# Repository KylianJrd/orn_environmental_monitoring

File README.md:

# orn_environmental_monitoring

ce projet va faire une station météo

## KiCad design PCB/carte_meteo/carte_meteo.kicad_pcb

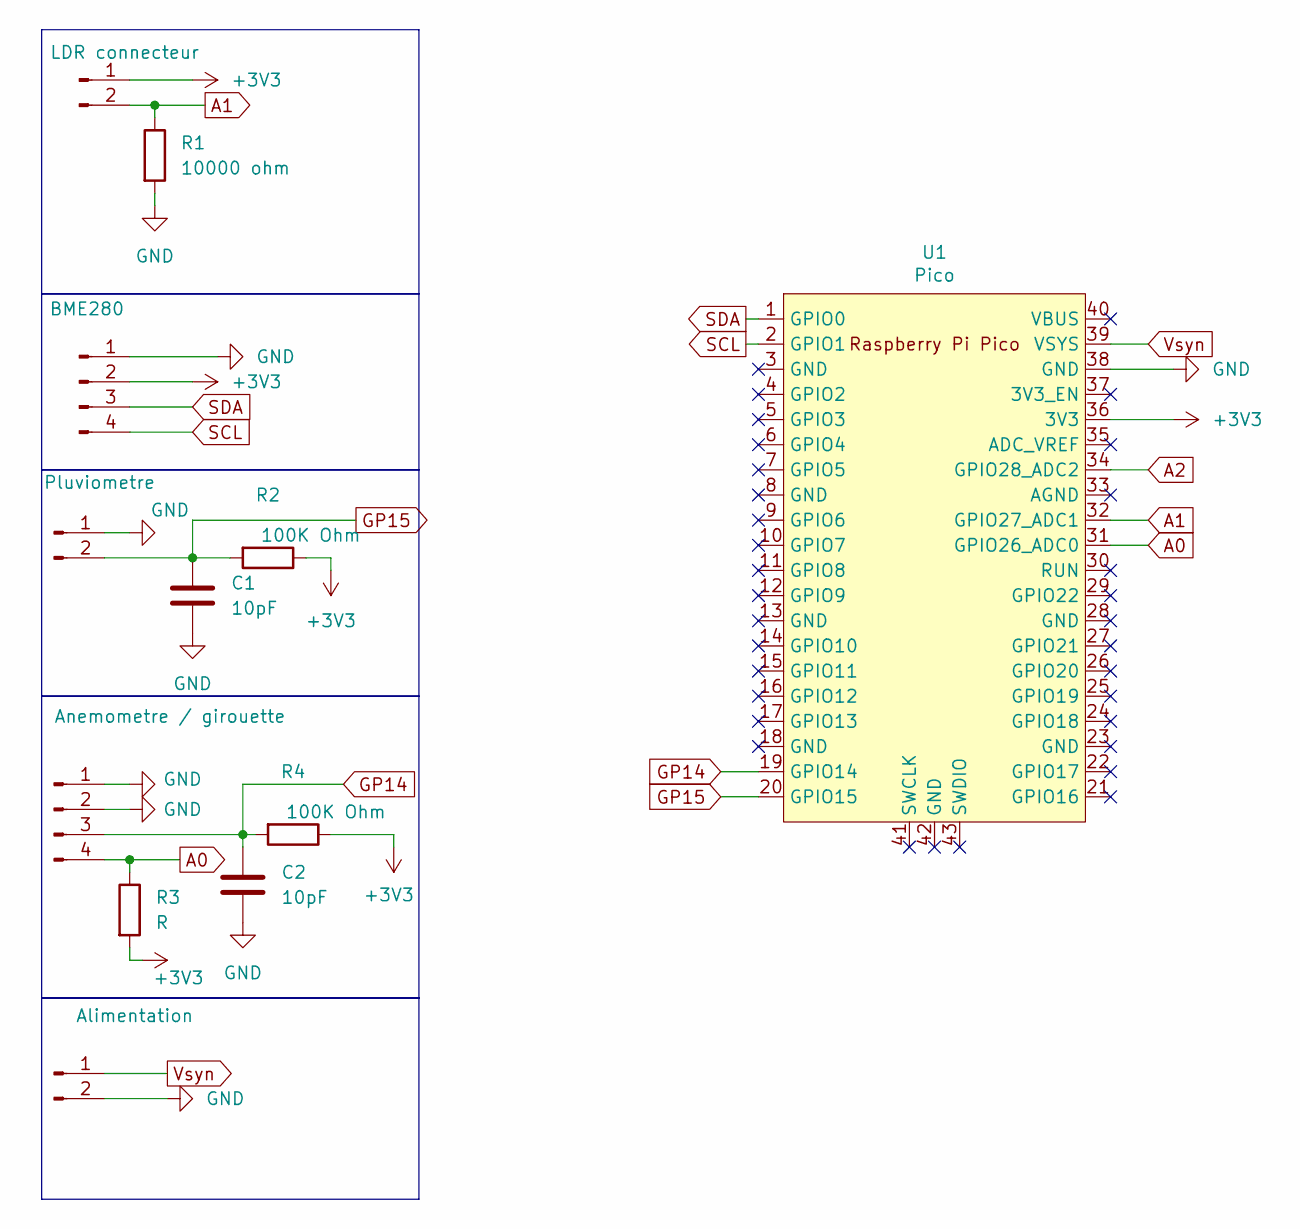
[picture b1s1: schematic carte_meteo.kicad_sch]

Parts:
C1, C2: 10pF; C_0805_2012Metric
J1: BME280; TerminalBlock_Phoenix_MKDS-1,5-4-5.08_1x04_P5.08mm_Horizont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
J2: LDR connecteur; TerminalBlock_Phoenix_MKDS-1,5-2-5.08_1x02_P5.08mm_Horizont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
J3: Pluviometre; TerminalBlock_Phoenix_MKDS-1,5-2-5.08_1x02_P5.08mm_Horizont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
J4: Anemometre / girouette; TerminalBlock_Phoenix_MKDS-1,5-4-5.08_1x04_P5.08mm_Horizont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
J5: Alimentation; TerminalBlock_Phoenix_MKDS-1,5-2-5.08_1x02_P5.08mm_Horizont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
R1: 10000 ohm; R_Axial_DIN0207_L6.3mm_D2.5mm_P10.16mm_Horizontal
R2, R4: 100K Ohm; R_Axial_DIN0207_L6.3mm_D2.5mm_P10.16mm_Horizontal
R3: R; R_Axial_DIN0207_L6.3mm_D2.5mm_P10.16mm_Horizontal
U1: Pico; RPi_Pico_SMD_TH

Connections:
+3V3: J1.2, J2.1, R2.1, R3.2, R4.1, U1.36 (3V3)
A0: J4.4, R3.1, U1.31 (GPIO26_ADC0)
A1: J2.2, R1.1, U1.32 (GPIO27_ADC1)
A2: U1.34 (GPIO28_ADC2)
GND: C1.2, C2.2, J1.1, J3.1, J4.1, J4.2, J5.2, R1.2, U1.38 (GND)
GP14: C2.1, J4.3, R4.2, U1.19 (GPIO14)
GP15: C1.1, J3.2, R2.2, U1.20 (GPIO15)
SCL: J1.4, U1.2 (GPIO1)
SDA: J1.3, U1.1 (GPIO0)
Vsyn: J5.1, U1.39 (VSYS)

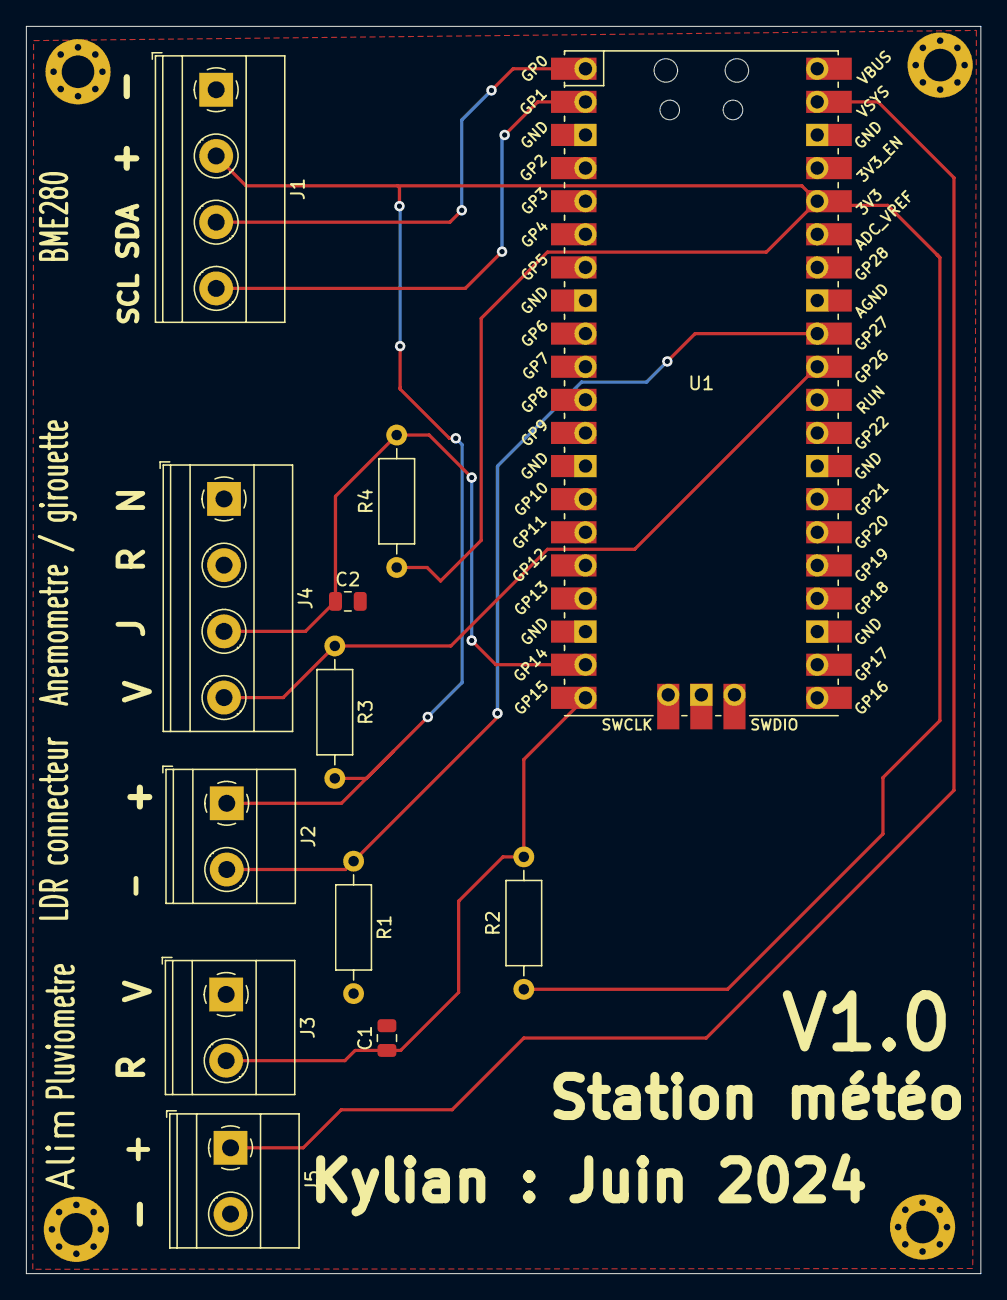
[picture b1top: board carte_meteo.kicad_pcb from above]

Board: 2 copper layers, 73.2 x 95.7 mm, 12 parts (0 on the bottom side), 9 nets.

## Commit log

2024-04-15 Add description of the project
2024-04-15 Add script BME280
2024-04-15 ajout du gitignore
2024-04-15 add script of LM35
2024-04-15 add script of DHT11
2024-04-15 rename of files
2024-04-15 add script ldr
2024-04-16 add script of LDR
2024-04-16 Modification code de la LDR
2024-04-16 add script of thermistance
2024-04-16 Add library of DS18B20 (sonde temperature)
2024-04-16 add script of DS18B20 (sonde temperature)
2024-04-17 ajout librairie pour sonde sht31
2024-04-17 add script of sonde sht31
2024-04-18 fichier mesure BME et SHT31
2024-04-18 Creation dossier mesure pour stocker les mesures
2024-04-18 Figure des donnée météorologiques du sht et du bme
2024-04-18 Sup fichier mesure
2024-04-18 add lib
2024-04-18 Modification du script pour le bme
2024-04-18 add script of Oled screen
2024-04-18 add script of all sensor
2024-04-25 add script of Wind direction
2024-04-25 add script of pluviometer
2024-04-25 change pin of lm35
2024-04-25 change pin of LDR
2024-04-25 add script of anemometer
2024-04-25 add script of all sensor for wind
2024-04-25 add all script of wind
2024-04-25 modification of script DHT11
2024-04-25 add mesure of 4 sensor, Wednesday 24 April 2024 at 16h31
2024-04-25 mesure of 4 sensor, Friday 19 April 2024 at 9h20
2024-04-29 add script json for all sensor
2024-05-22 add config files
2024-05-22 add biblio wind sensor
2024-05-22 add biblio BME
2024-05-22 add LDR Biblio
2024-05-22 add final script
2024-05-27 add pcb of project
2024-05-27 add project of pcb
2024-05-27 add schematic of pcb
2024-06-13 modification code anemomtre
2024-06-13 mesure capteur
2024-06-13 carte mere kicad
2024-06-13 code main
2024-06-13 code main version beta
2024-06-13 modif code kit capteur vent
2024-06-13 code bme280
2024-06-13 notebook plot mesure
